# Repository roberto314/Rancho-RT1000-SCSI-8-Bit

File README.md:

# Rancho-RT1000-SCSI-8-Bit
Recreation of a bootable ISA 8-Bit SCSI Card.

There can be one PAL on the Card (GAL20L8), this is for the floppy part only.
BIOS EPROM is a 27C128 Type, but only 8k are used.

[Schematic](schematic/Rancho%20RT1000/pdf/Rancho%20RT1000%20SCSI%20Controller.pdf)

For now there is no plan to manufacture the board.

| BIOS Ver.   |   8088/80C88        |    NEC V20       |   286      |  386SX     |
|-------------|---------------------|------------------|------------|------------|
| Rancho 8.10 | no boot, no ASPI    | no boot, no ASPI | boots+ASPI | boots+ASPI |
| Rancho 8.20 | no boot, no ASPI    | no boot, no ASPI | boots+ASPI | boots+ASPI |
| Corel 1.65  | no boot, Corel ASPI | boots+Corel ASPI | boots+ASPI | boots+ASPI |

Comment: On an XT, even with V20 CPU, with Rancho BIOS, a Disk is found but hangs when trying to boot. RTASPI10.SYS says it needs a 286.

The Card seems to be the same as the Corel LS2000, so i tried the Corel BIOS and it works!

Unfortunately the Corel uses a different CHS Conversion, so the Rancho Images won't work.

The ASPI Driver from the Rancho (RTASPI10.SYS) works with the Corel BIOS and vice versa, BUT they need the correct CHS Values!

The ASPI Driver from the Corel (ASPILS_D.SYS) works with a V20 CPU and with an 8088.
The ASPIDISK.SYS Driver doesn't like the 8088 BUT the Trantor TSCSI Disk Driver in Version 4.53 works (Filename: TSCSI.453)

The Rancho BIOS doesn't need an Interrupt, the Corel BIOS seems to work only with IRQ4!
The Jumper X14, X15, X16, X17 and X18 won't do anything with the Corel BIOS.

With the BIOS EPROM installed the 8088 hangs during boot from Floppy! One has to disable the BIOS in order to boot on an 8088.

The Corel BIOS can only address two Harddisks without an ASPI Driver installed!

Heads and Sectors working with original RT1000 BIOS (v8.20):

Tested with MSDOS 5 and with a 386SX and does NOT work with an 8088 nor 80C88!:

(spc = Sectors/Cluster, spf = Sectors/FAT)

* C: 1023 / H:2  / S:32 32 MB (FAT16/4) spc=4,spf=0x40: works
* C: 1023 / H:4  / S:32 64 MB (FAT16/6) spc=4,spf=0x80: non-system disk
* C:  511 / H:8  / S:32 64 MB (FAT16/6) spc=4,spf=0x80: non-system disk
* C: 1015 / H:3  / S:43 65510 kB (FAT16/6) spc=4,spf=0x80: works
* C: 1023 / H:8  / S:32 128 MB (FAT16/6) spc=4,spf=0x100: non-system disk
* C: 1007 / H:5  / S:52 127.8 MB (FAT16/6) spc=4,spf=0x100: works
* C: 1021 / H:9  / S:57 261800 kB (FAT16/6) spc=8,spf=0x100: works
* C: 1023 / H:9  / S:57 262627 kB (FAT16/6) spc=16,spf=0x100: non-system disk
* C: 1010 / H:17  / S:60 515072 kB (FAT16/6) spc=16,spf=0xFC: works
* C: 1011 / H:31  / S:62 948 MB (FAT16/6) spc=32,spf=0xEE: works

Heads and Sectors working with Corel LS2000 BIOS (v1.65):

Tested with 386SX and does NOT work with an 8088!:

* C:  961 / H:17 / S:8 63.1 MB (FAT16/6) spc=4,spf=0x80: works
* C:  961 / H:17 / S:16 127.6 MB (FAT16/6) spc=4,spf=0xFF: works
* C: 1021 / H:32 / S:16 255.5 MB (FAT16/6) spc=16,spf=0x80: works
* C:  597 / H:64 / S:16 299 MB (FAT16/6) spc=16,spf=0x96: works
* C: 1003 / H:64 / S:16 502 MB (FAT16/6) spc=16,spf=0xFB: works
* C: 1019 / H:64 / S:16 509.9 MB (FAT16/6) spc=16,spf=0xFF: works
* C:  570 / H:64 / S:32 570.5 MB (FAT16/6) spc=32,spf=0x8F: works
* C:  571 / H:64 / S:32 572 MB (FAT16/6) spc=32,spf=0x8F: works
* C:  667 / H:64 / S:32 668 MB (FAT16/6) spc=32,spf=0xA7: works
* C:  762 / H:64 / S:32 763 MB (FAT16/6) spc=32,spf=0xBF: works
* C:  859 / H:64 / S:32 860 MB (FAT16/6) spc=32,spf=0xD7: works
* C:  903 / H:64 / S:32 904 MB (FAT16/6) spc=32,spf=0xE2: works
* C:  927 / H:64 / S:32 927.9 MB (FAT16/6) spc=32,spf=0xE8: works
* C: 1019 / H:64 / S:32 1020 MB (FAT16/6) spc=32,spf=0xFF: works
* C:  946 / H:64 / S:32 947 MB (FAT16/6) spc=32,spf=0xED: doesn't work
* C:  946 / H:64 / S:32 947 MB (FAT16/6) spc=32,spf=0xFB: doesn't work

It should be said that the Corel Drivers and BIOS is the way to go!

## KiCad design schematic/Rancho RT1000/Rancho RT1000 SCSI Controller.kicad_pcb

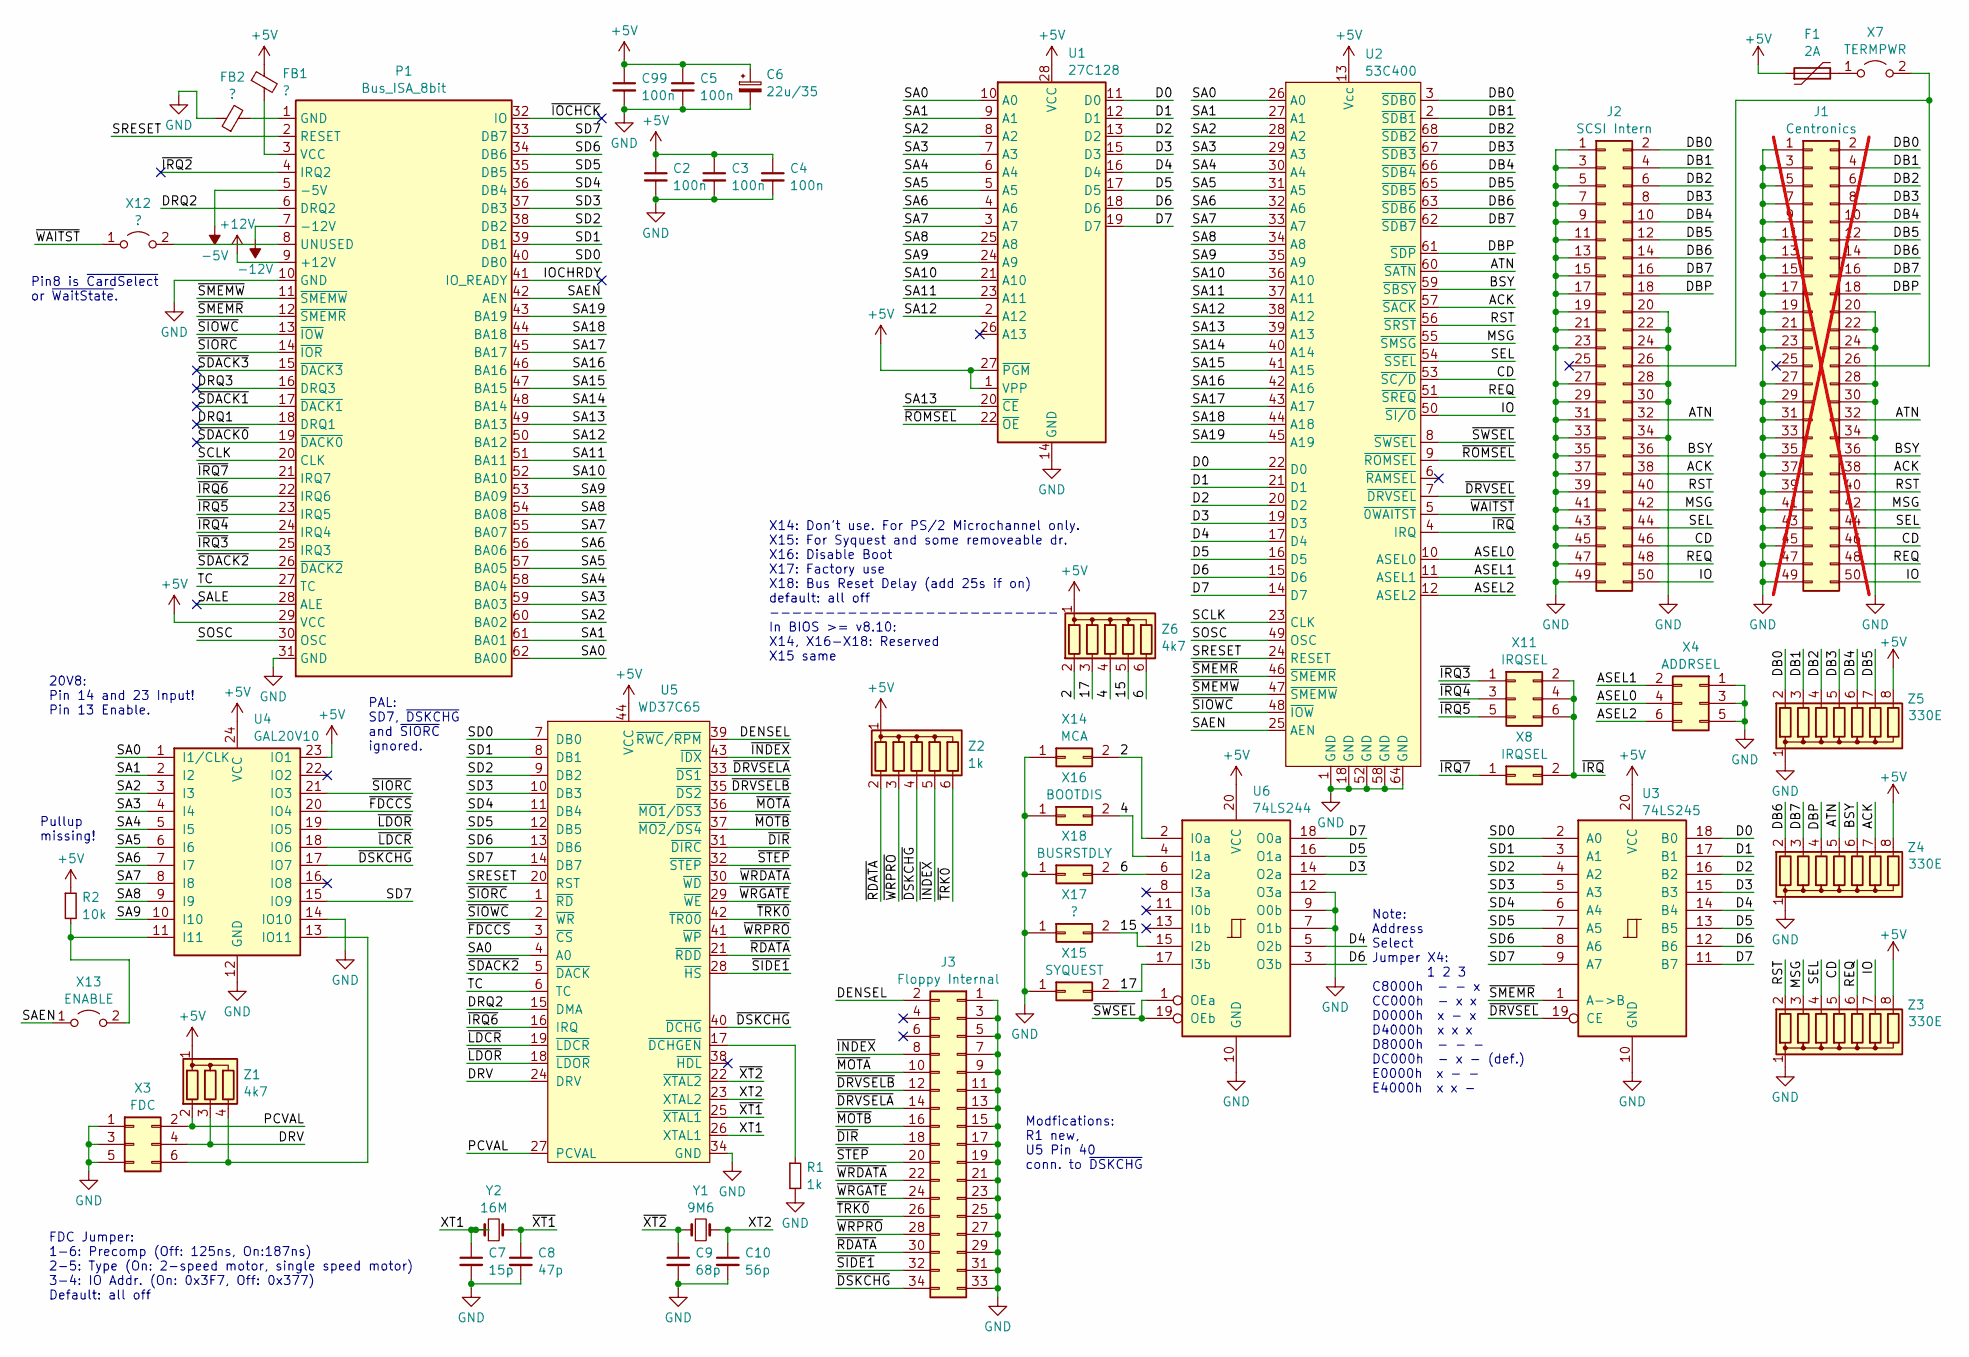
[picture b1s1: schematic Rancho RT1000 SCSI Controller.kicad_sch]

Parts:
C2, C3, C4, C5: 100n; C_Axial_L3.8mm_D2.6mm_P12.50mm_Horizontal
C6: 22u/35; C_Axial_L12.0mm_D6.5mm_P20.00mm_Horizontal
C7: 15p; C_Axial_L3.8mm_D2.6mm_P12.50mm_Horizontal
C8: 47p; C_Axial_L3.8mm_D2.6mm_P12.50mm_Horizontal
C9: 68p; C_Axial_L3.8mm_D2.6mm_P12.50mm_Horizontal
C10: 56p; C_Axial_L3.8mm_D2.6mm_P12.50mm_Horizontal
C99: 100n; C_Rect_L9.0mm_W2.5mm_P7.50mm_MKT
F1: 2A; L_Axial_L5.3mm_D2.2mm_P10.16mm_Horizontal_Vishay_IM-1
FB1, FB2: ?; L_Axial_L5.3mm_D2.2mm_P10.16mm_Horizontal_Vishay_IM-1
J1: Centronics; PinHeader_2x25_P2.54mm_Vertical; not fitted
J2: SCSI Intern; PinHeader_2x25_P2.54mm_Vertical
J3: Floppy Internal; PinHeader_2x17_P2.54mm_Vertical
P1: Bus_ISA_8bit; BUS_XT
R1: 1k; R_Axial_DIN0309_L9.0mm_D3.2mm_P12.70mm_Horizontal
R2: 10k; R_Axial_DIN0309_L9.0mm_D3.2mm_P12.70mm_Horizontal
U1: 27C128; DIP-28_W15.24mm_Socket_LongPads
U2: 53C400; PLCC-68_THT-Socket
U3: 74LS245; DIP-20_W7.62mm_LongPads
U4: GAL20V10; DIP-24_W7.62mm_Socket_LongPads
U5: WD37C65; PLCC-44_THT-Socket
U6: 74LS244; DIP-20_W7.62mm_LongPads
X3: FDC; PinHeader_2x03_P2.54mm_Vertical
X4: ADDRSEL; PinHeader_2x03_P2.54mm_Vertical
X7: TERMPWR; PinHeader_2x01_P2.54mm_Vertical
X8: IRQSEL; PinHeader_2x01_P2.54mm_Vertical
X11: IRQSEL; PinHeader_2x03_P2.54mm_Vertical
X12, X17: ?; PinHeader_2x01_P2.54mm_Vertical
X13: ENABLE; PinHeader_2x01_P2.54mm_Vertical
X14: MCA; PinHeader_2x01_P2.54mm_Vertical
X15: SYQUEST; PinHeader_2x01_P2.54mm_Vertical
X16: BOOTDIS; PinHeader_2x01_P2.54mm_Vertical
X18: BUSRSTDLY; PinHeader_2x01_P2.54mm_Vertical
Y1: 9M6; Crystal_HC49-U_Vertical
Y2: 16M; Crystal_HC49-U_Vertical
Z1: 4k7; R_Array_SIP4
Z2: 1k; R_Array_SIP6
Z3, Z4, Z5: 330E; R_Array_SIP8
Z6: 4k7; R_Array_SIP6

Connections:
+5V: C2.1, C3.1, C4.1, C5.1, C6.1, C99.1, F1.1, FB1.1, P1.29 (VCC), R2.1, U1.1 (VPP), U1.27 (~PGM), U1.28 (VCC), U2.13 (Vcc), U3.20 (VCC), U4.23 (IO1), U4.24 (VCC), U5.44 (VCC), U6.20 (VCC), Z1.1 (common), Z2.1 (common), Z3.8 (R7), Z4.8 (R7), Z5.8 (R7), Z6.1 (common)
+12V: P1.9 (+12V)
-5V: P1.5 (-5V)
-12V: P1.7 (-12V)
/2: U6.2 (I0a), X14.2, Z6.2 (R1)
/4: U6.4 (I1a), X16.2, Z6.4 (R3)
/6: U6.6 (I2a), X18.2, Z6.6 (R5)
/15: U6.15 (I2b), X17.2, Z6.5 (R4)
/17: U6.17 (I3b), X15.2, Z6.3 (R2)
/ACK: J1.38, J2.38, U2.57 (~SACK), Z4.7 (R6)
/ASEL0: U2.10 (ASEL0), X4.4
/ASEL1: U2.11 (ASEL1), X4.2
/ASEL2: U2.12 (ASEL2), X4.6
/ATN: J1.32, J2.32, U2.60 (~SATN), Z4.5 (R4)
/BSY: J1.36, J2.36, U2.59 (~SBSY), Z4.6 (R5)
/CD: J1.46, J2.46, U2.53 (~SC/D), Z3.5 (R4)
/D0: U1.11 (D0), U2.22 (D0), U3.18 (B0)
/D1: U1.12 (D1), U2.21 (D1), U3.17 (B1)
/D2: U1.13 (D2), U2.20 (D2), U3.16 (B2)
/D3: U1.15 (D3), U2.19 (D3), U3.15 (B3), U6.14 (O2a)
/D4: U1.16 (D4), U2.17 (D4), U3.14 (B4), U6.5 (O2b)
/D5: U1.17 (D5), U2.16 (D5), U3.13 (B5), U6.16 (O1a)
/D6: U1.18 (D6), U2.15 (D6), U3.12 (B6), U6.3 (O3b)
/D7: U1.19 (D7), U2.14 (D7), U3.11 (B7), U6.18 (O0a)
/DB0: J1.2, J2.2, U2.3 (~SDB0), Z5.2 (R1)
/DB1: J1.4, J2.4, U2.2 (~SDB1), Z5.3 (R2)
/DB2: J1.6, J2.6, U2.68 (~SDB2), Z5.4 (R3)
/DB3: J1.8, J2.8, U2.67 (~SDB3), Z5.5 (R4)
/DB4: J1.10, J2.10, U2.66 (~SDB4), Z5.6 (R5)
/DB5: J1.12, J2.12, U2.65 (~SDB5), Z5.7 (R6)
/DB6: J1.14, J2.14, U2.63 (~SDB6), Z4.2 (R1)
/DB7: J1.16, J2.16, U2.62 (~SDB7), Z4.3 (R2)
/DBP: J1.18, J2.18, U2.61 (~SDP), Z4.4 (R3)
/DENSEL: J3.2, U5.39 (~RWC/~RPM)
/DRQ1: P1.18 (DRQ1)
/DRQ2: P1.6 (DRQ2), U5.15 (DMA)
/DRQ3: P1.16 (DRQ3)
/DRV: U5.24 (DRV), X3.4, Z1.3 (R2)
/IO: J1.50, J2.50, U2.50 (~SI/O), Z3.7 (R6)
/IOCHRDY: P1.41 (IO_READY)
/MSG: J1.42, J2.42, U2.55 (~SMSG), Z3.3 (R2)
/PCVAL: U5.27 (PCVAL), X3.2, Z1.2 (R1)
/REQ: J1.48, J2.48, U2.51 (~SREQ), Z3.6 (R5)
/RST: J1.40, J2.40, U2.56 (~SRST), Z3.2 (R1)
/SA0: P1.62 (BA00), U1.10 (A0), U2.26 (A0), U4.1 (I1/CLK), U5.4 (A0)
/SA1: P1.61 (BA01), U1.9 (A1), U2.27 (A1), U4.2 (I2)
/SA2: P1.60 (BA02), U1.8 (A2), U2.28 (A2), U4.3 (I3)
/SA3: P1.59 (BA03), U1.7 (A3), U2.29 (A3), U4.4 (I4)
/SA4: P1.58 (BA04), U1.6 (A4), U2.30 (A4), U4.5 (I5)
/SA5: P1.57 (BA05), U1.5 (A5), U2.31 (A5), U4.6 (I6)
/SA6: P1.56 (BA06), U1.4 (A6), U2.32 (A6), U4.7 (I7)
/SA7: P1.55 (BA07), U1.3 (A7), U2.33 (A7), U4.8 (I8)
/SA8: P1.54 (BA08), U1.25 (A8), U2.34 (A8), U4.9 (I9)
/SA9: P1.53 (BA09), U1.24 (A9), U2.35 (A9), U4.10 (I10)
/SA10: P1.52 (BA10), U1.21 (A10), U2.36 (A10)
/SA11: P1.51 (BA11), U1.23 (A11), U2.37 (A11)
/SA12: P1.50 (BA12), U1.2 (A12), U2.38 (A12)
/SA13: P1.49 (BA13), U1.20 (~CE), U2.39 (A13)
/SA14: P1.48 (BA14), U2.40 (A14)
/SA15: P1.47 (BA15), U2.41 (A15)
/SA16: P1.46 (BA16), U2.42 (A16)
/SA17: P1.45 (BA17), U2.43 (A17)
/SA18: P1.44 (BA18), U2.44 (A18)
/SA19: P1.43 (BA19), U2.45 (A19)
/SAEN: P1.42 (AEN), U2.25 (AEN), X13.1 (A)
/SALE: P1.28 (ALE)
/SCLK: P1.20 (CLK), U2.23 (CLK)
/SD0: P1.40 (DB0), U3.2 (A0), U5.7 (DB0)
/SD1: P1.39 (DB1), U3.3 (A1), U5.8 (DB1)
/SD2: P1.38 (DB2), U3.4 (A2), U5.9 (DB2)
/SD3: P1.37 (DB3), U3.5 (A3), U5.10 (DB3)
/SD4: P1.36 (DB4), U3.6 (A4), U5.11 (DB4)
/SD5: P1.35 (DB5), U3.7 (A5), U5.12 (DB5)
/SD6: P1.34 (DB6), U3.8 (A6), U5.13 (DB6)
/SD7: P1.33 (DB7), U3.9 (A7), U4.15 (IO9), U5.14 (DB7)
/SEL: J1.44, J2.44, U2.54 (~SSEL), Z3.4 (R3)
/SOSC: P1.30 (OSC), U2.49 (OSC)
/SRESET: P1.2 (RESET), U2.24 (RESET), U5.20 (RST)
/TC: P1.27 (TC), U5.6 (TC)
/XT1: C7.1, U5.26 (XTAL1), Y2.1
/XT2: C10.1, U5.23 (XTAL2), Y1.2
/~DIR: J3.18, U5.31 (~DIRC)
/~DRVSELA: J3.14, U5.33 (~DS1)
/~DRVSELB: J3.12, U5.35 (~DS2)
/~DRVSEL: U2.7 (~DRVSEL), U3.19 (CE)
/~DSKCHG: J3.34, U4.17 (IO7), U5.40 (~DCHG), Z2.4 (R3)
/~FDCCS: U4.20 (IO4), U5.3 (~CS)
/~INDEX: J3.8, U5.43 (~IDX), Z2.5 (R4)
/~IOCHCK: P1.32 (IO)
/~IRQ2: P1.4 (IRQ2)
/~IRQ3: P1.25 (IRQ3), X11.1
/~IRQ4: P1.24 (IRQ4), X11.3
/~IRQ5: P1.23 (IRQ5), X11.5
/~IRQ6: P1.22 (IRQ6), U5.16 (IRQ)
/~IRQ7: P1.21 (IRQ7), X8.1
/~IRQ: U2.4 (IRQ), X8.2, X11.2, X11.4, X11.6
/~LDCR: U4.18 (IO6), U5.19 (~LDCR)
/~LDOR: U4.19 (IO5), U5.18 (~LDOR)
/~MOTA: J3.10, U5.36 (~MO1/~DS3)
/~MOTB: J3.16, U5.37 (~MO2/~DS4)
/~RDATA: J3.30, U5.21 (~RDD), Z2.2 (R1)
/~ROMSEL: U1.22 (~OE), U2.9 (~ROMSEL)
/~SDACK0: P1.19 (~DACK0)
/~SDACK1: P1.17 (~DACK1)
/~SDACK2: P1.26 (~DACK2), U5.5 (~DACK)
/~SDACK3: P1.15 (~DACK3)
/~SIDE1: J3.32, U5.28 (~HS)
/~SIORC: P1.14 (~IOR), U4.21 (IO3), U5.1 (~RD)
/~SIOWC: P1.13 (~IOW), U2.48 (~IOW), U5.2 (~WR)
/~SMEMR: P1.12 (~SMEMR), U2.46 (~SMEMR), U3.1 (A->B)
/~SMEMW: P1.11 (~SMEMW), U2.47 (~SMEMW)
/~STEP: J3.20, U5.32 (~STEP)
/~SWSEL: U2.8 (~SWSEL), U6.1 (OEa), U6.19 (OEb)
/~TRK0: J3.26, U5.42 (~TR00), Z2.6 (R5)
/~WAITST: U2.5 (~0WAITST), X12.1 (A)
/~WRDATA: J3.22, U5.30 (~WD)
/~WRGATE: J3.24, U5.29 (~WE)
/~WRPRO: J3.28, U5.41 (~WP), Z2.3 (R2)
/~XT1: C8.1, U5.25 (~XTAL1), Y2.2
/~XT2: C9.1, U5.22 (~XTAL2), Y1.1
GND: C2.2, C3.2, C4.2, C5.2, C6.2, C7.2, C8.2, C9.2, C10.2, C99.2, FB2.1, J1.1, J1.3, J1.5, J1.7, J1.9, J1.11, J1.13, J1.15, J1.17, J1.19, J1.20, J1.21, J1.22, J1.23, J1.24, J1.27, J1.28, J1.29, J1.30, J1.31, J1.33, J1.34, J1.35, J1.37, J1.39, J1.41, J1.43, J1.45, J1.47, J1.49, J2.1, J2.3, J2.5, J2.7, J2.9, J2.11, J2.13, J2.15, J2.17, J2.19, J2.20, J2.21, J2.22, J2.23, J2.24, J2.27, J2.28, J2.29, J2.30, J2.31, J2.33, J2.34, J2.35, J2.37, J2.39, J2.41, J2.43, J2.45, J2.47, J2.49, J3.1, J3.3, J3.5, J3.7, J3.9, J3.11, J3.13, J3.15, J3.17, J3.19, J3.21, J3.23, J3.25, J3.27, J3.29, J3.31, J3.33, P1.10 (GND), P1.31 (GND), R1.2, U1.14 (GND), U2.1 (GND), U2.18 (GND), U2.52 (GND), U2.58 (GND), U2.64 (GND), U3.10 (GND), U4.12 (GND), U4.14 (IO10), U5.34 (GND), U6.7 (O1b), U6.9 (O0b), U6.10 (GND), U6.12 (O3a), X3.1, X3.3, X3.5, X4.1, X4.3, X4.5, X14.1, X15.1, X16.1, X17.1, X18.1, Z3.1 (common), Z4.1 (common), Z5.1 (common)
unnamed: FB1.2, P1.3 (VCC)
unnamed: FB2.2, P1.1 (GND)
unnamed: J1.26, J2.26, X7.2 (B)
unnamed: P1.8 (UNUSED), X12.2 (B)
unnamed: R2.2, U4.11 (I11), X13.2 (B)
unnamed: U4.13 (IO11), X3.6, Z1.4 (R3)
unnamed: R1.1, U5.17 (~DCHGEN)
unnamed: F1.2, X7.1 (A)

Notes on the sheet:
Pullup missing!
X14: Don't use. For PS/2 Microchannel only. X15: For Syquest and some removeable dr. X16: Disable Boot X17: Factory use X18: Bus Reset Delay (add 25s if on) default: all off -------------------------- In BIOS >= v8.10: X14, X16-X18: Reserved X15 same
FDC Jumper: 1-6: Precomp (Off: 125ns, On:187ns) 2-5: Type (On: 2-speed motor, single speed motor) 3-4: IO Addr. (On: 0x3F7, Off: 0x377) Default: all off
Modfications: R1 new, U5 Pin 40 conn. to ~{DSKCHG}
Note: Address Select Jumper X4: 1 2 3 C8000h - - x CC000h - x x D0000h x - x D4000h x x x D8000h - - - DC000h - x - (def.) E0000h x - - E4000h x x -
PAL: SD7, ~{DSKCHG} and ~{SIORC} ignored.
Pin8 is ~{CardSelect} or ~{WaitState}.
20V8: Pin 14 and 23 Input! Pin 13 Enable.

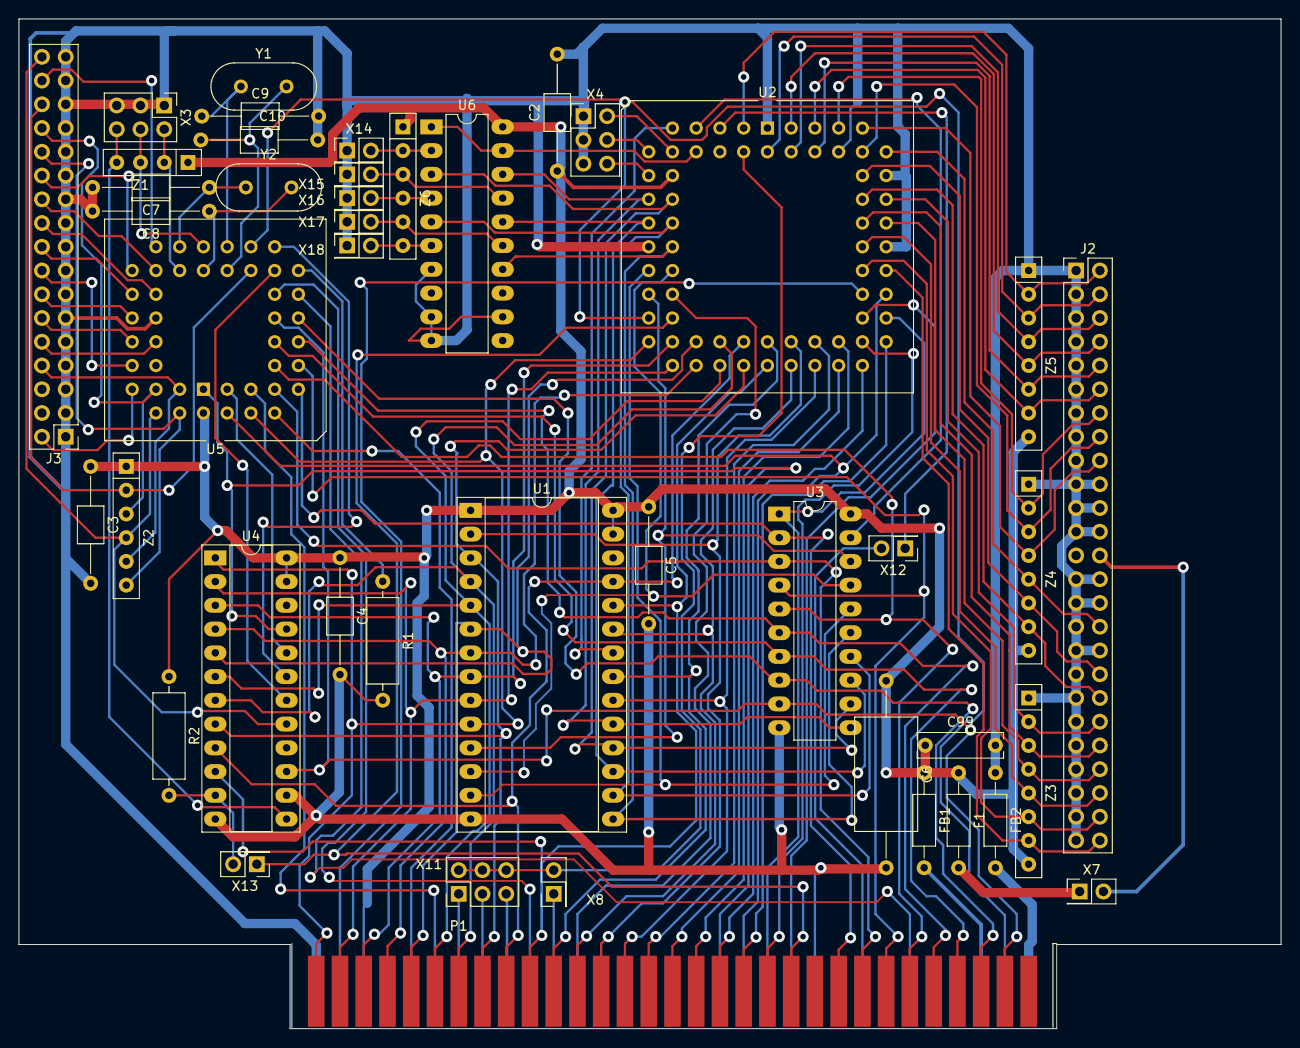
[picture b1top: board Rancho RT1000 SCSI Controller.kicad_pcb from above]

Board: 2 copper layers, 135.0 x 108.0 mm, 44 parts (0 on the bottom side), 117 nets.

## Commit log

2024-04-23 Layout finished, pics updated
2024-04-23 Readme updated
2024-04-26 more images tested, 948MB is max now
2024-05-02 more Images tested.
2024-05-02 Readme update
2024-05-02 Corel BIOS added
2024-05-11 more Testing with Corel BIOS
2024-05-11 more Testing with Corel BIOS, Pics added, 8088 works
2024-05-11 Pics added
2024-05-14 nothing new
